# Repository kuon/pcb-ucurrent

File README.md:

# THIS REPOSITORY HAS MOVED

New URL: https://git.goyman.com/kuon/pcb-ucurrent

Why I moved everything out of GitHub:

https://github.com/kuon/WhyILeftGithub/blob/main/README.md

----

# µcurrent board

This is my own PCB for the µcurrent board.

It is based on <https://www.eevblog.com/projects/ucurrent/>.

While the base idea is the same, a few things have been modified:

- There is a rotary switch which can support many different shunt resistor, 12
  in the current design.
- The power supply has been modified to use ±15V to give a greater range.
- The amplifier has been modified to match the power supply.

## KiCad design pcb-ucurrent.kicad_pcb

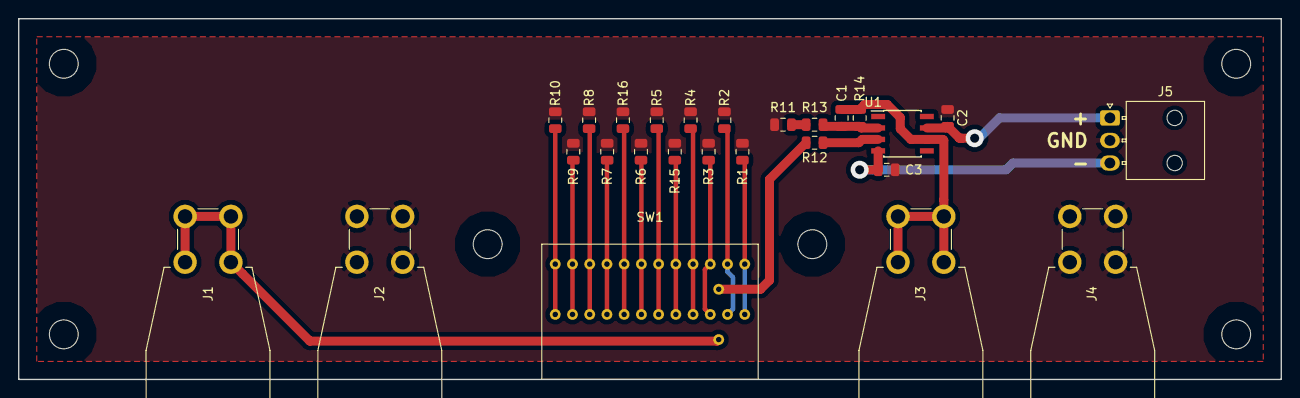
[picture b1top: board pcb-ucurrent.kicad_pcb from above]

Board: 2 copper layers, 140.0 x 40.0 mm, 26 parts (0 on the bottom side), 21 nets.

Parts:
C1: 150p; C_0805_2012Metric
C2, C3: 100n; C_0805_2012Metric
J1: IN+; CalTest_CT3151
J2: IN-; CalTest_CT3151
J3: OUT+; CalTest_CT3151
J4: OUT-; CalTest_CT3151
J5: Conn_01x03_Male; Molex_Nano-Fit_105313-xx03_1x03_P2.50mm_Horizontal
R1: 500m; R_0805_2012Metric
R2: 1R; R_0805_2012Metric
R3: 5R; R_0805_2012Metric
R4: 10R; R_0805_2012Metric
R5: 50R; R_0805_2012Metric
R6: 100R; R_0805_2012Metric
R7: 500R; R_0805_2012Metric
R8: 1k; R_0805_2012Metric
R9: 5k; R_0805_2012Metric
R10, R12: 10k; R_0805_2012Metric
R11: 680R; R_0805_2012Metric
R13: 330R; R_0805_2012Metric
R14: 100k; R_0805_2012Metric
R15: 20R; R_0805_2012Metric
R16: 200R; R_0805_2012Metric
SW1: 71BDF30-02-1
U1: OPA189ID; SOIC-8_3.9x4.9mm_P1.27mm

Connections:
+VDC: C2.2, J5.1, U1.7
-VDC: C3.2, J5.3, U1.4
/IN+: J1.1, SW1.1
/OUT+: C1.1, J3.1, R14.1, U1.6
GND: C2.1, C3.1, J2.1, J4.1, J5.2, R1.1, R2.1, R3.1, R4.1, R5.1, R6.1, R7.1, R8.1, R9.1, R10.1, R11.2, R15.1, R16.1
unnamed: C1.2, R13.1, R14.2, U1.2
unnamed: R1.2, SW1.2, SW1.15
unnamed: R2.2, SW1.3, SW1.16
unnamed: R3.2, SW1.4, SW1.17
unnamed: R4.2, SW1.5, SW1.18
unnamed: R5.2, SW1.7, SW1.20
unnamed: R6.2, SW1.8, SW1.21
unnamed: R7.2, SW1.10, SW1.23
unnamed: R8.2, SW1.11, SW1.24
unnamed: R9.2, SW1.12, SW1.25
unnamed: R10.2, SW1.13, SW1.26
unnamed: R11.1, R13.2
unnamed: R12.1, U1.3
unnamed: R12.2, SW1.14
unnamed: R15.2, SW1.6, SW1.19
unnamed: R16.2, SW1.9, SW1.22

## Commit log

2019-02-11 PCB for my own µcurrent board
2019-02-11 Add README
2019-05-21 Update design
2020-10-26 Moved away from github
